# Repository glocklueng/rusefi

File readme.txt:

current binaries are always available at http://rusefi.com/build_server/

*****************************************************************************
*** Releases                                                              ***
*****************************************************************************
07/06/2015	r8554	more CAN, better console, bugfixes, performance
04/26/2015	r7938	vehicle speed sensor, stepper idle valve, lots of improvements
11/13/2014	r5327	ChibiOS/RT 2.6.6, better cold start logic, bugfixes, bugfixes, bugfixes...
06/12/2014	r3477	Precise event scheduling, protocol selection 
03/26/2014	r2413	C++, refactoring & improvements
02/23/2013	r1777	trigger is now configurable via TunerStudio
01/30/2014	r1309	true trigger angles, VBatt signal
01/12/2014	r1007	refactoring, refactoring & refactoring
12/19/2013	r605	ignition control & a little bit of CAN bus
11/08/2013	r100	Tuner Studio fuel map tuning, fuel pump control
10/14/2013	r39	USB serial bug, missing IAR files, self-containted Makefile
10/13/2013	r33	IAR project file
10/04/2013	r26	Patched ChibiOS/RT 2.6.1 sources are now included
09/23/2013	r20	Tuner Studio integration, configuraton persistence
08/30/2013	r14	initial documentation & refactoring. tunerstudio integration
08/03/2013	r13	wideband O2 input, better idling algorithm, serial-over-USB
07/05/2013	r10	Second CKP, sequential injection.
06/19/2013	r9	Initial version - batch injection & ignition with advance table lookup.

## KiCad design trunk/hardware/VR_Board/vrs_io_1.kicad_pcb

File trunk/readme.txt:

current binaries are always available at http://rusefi.com/build_server/

#Releases

| Release date  | Revision  | Details |
| ------------  | --------- | ------- |
| 02/15/2016	| r9600     | automatic warm-up fuel correction, performance improvements
| 08/31/2015	| r8725     | acceleration fuel correction, console improvements
| 07/06/2015	| r8554     | more CAN, better console, bugfixes, performance
| 04/26/2015	| r7938	    | vehicle speed sensor, stepper idle valve, lots of improvements
| 11/13/2014	| r5327	    | ChibiOS/RT 2.6.6, better cold start logic, bugfixes, bugfixes, bugfixes...
| 06/12/2014	| r3477	    | Precise event scheduling, protocol selection 
| 03/26/2014	| r2413	    | C++, refactoring & improvements
| 02/23/2013	| r1777	    | trigger is now configurable via TunerStudio
| 01/30/2014	| r1309	    | true trigger angles, VBatt signal
| 01/12/2014	| r1007	    | refactoring, refactoring & refactoring
| 12/19/2013	| r605	    | ignition control & a little bit of CAN bus
| 11/08/2013	| r100	    | Tuner Studio fuel map tuning, fuel pump control
| 10/14/2013	| r39	    | USB serial bug, missing IAR files, self-containted Makefile
| 10/13/2013	| r33	    | IAR project file
| 10/04/2013	| r26	    | Patched ChibiOS/RT 2.6.1 sources are now included
| 09/23/2013	| r20	    | Tuner Studio integration, configuraton persistence
| 08/30/2013	| r14	    | initial documentation & refactoring. tunerstudio integration
| 08/03/2013	| r13	    | wideband O2 input, better idling algorithm, serial-over-USB
| 07/05/2013	| r10	    | Second CKP, sequential injection.
| 06/19/2013	| r9	    | Initial version - batch injection & ignition with advance table lookup.

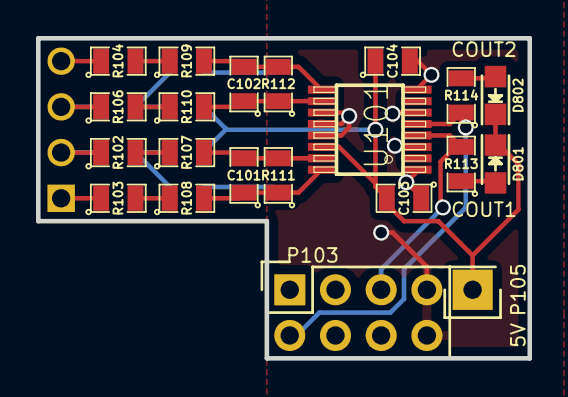
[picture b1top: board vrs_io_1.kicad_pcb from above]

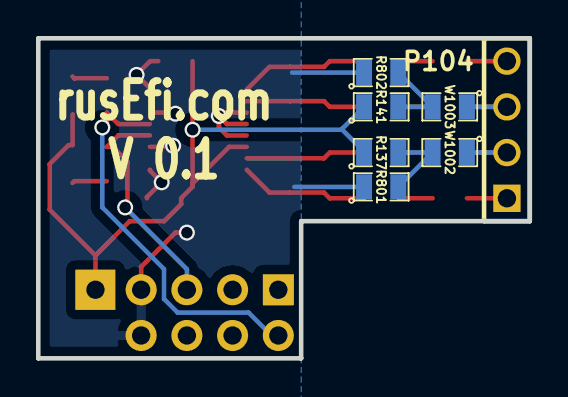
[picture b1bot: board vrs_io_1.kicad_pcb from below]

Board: 2 copper layers, 27.3 x 17.8 mm, 28 parts (7 on the bottom side), 20 nets.

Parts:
C101, C102: 1000pF; SM0805
C103: 10uF; SM0805
C104: 0.1uF; SM0805
D801, D802: LED-red; LED_0805
P103: CONN_02X04; Socket_Strip_Straight_2x04
P104: CONN_4; PIN_ARRAY_4x1
P105: CONN_01X01; Socket_Strip_Straight_1x01
R102, R103, R104, R106, R107, R108, R109, R110, R111, R112: 5k; SM0805
R113, R114: 10k; SM0805
R137, R141: 1K; SM0805
R801, R802: pdwn; SM0805
U101: MAX9926/9927; maxim-10-QSOP16
W1002, W1003: JMP; SM0805

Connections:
/5V: C103.2, C104.1, D801.1, D802.1, P105.1, R137.1, R141.1, U101.14
/CAM+: P104.4, R104.1
/CAM-: P104.3, R106.1, W1003.1
/CRK2+: P104.1, R103.1
/CRK2-: P104.2, R102.1, W1002.1
/Cout1: P103.5, R113.2, U101.4
/Cout2: P103.2, R114.1, U101.5
GND: C103.1, C104.2, P103.7, P103.8, R801.1, R802.1, U101.1, U101.3, U101.6, U101.8, U101.11, U101.12, U101.13
unnamed: C101.1, R108.2, R111.1, U101.16
unnamed: C101.2, R107.2, R111.2, U101.15
unnamed: C102.1, R110.2, R112.1, U101.10
unnamed: C102.2, R109.2, R112.2, U101.9
unnamed: D801.2, R113.1
unnamed: D802.2, R114.2
unnamed: R102.2, R107.1
unnamed: R103.2, R108.1
unnamed: R104.2, R109.1
unnamed: R106.2, R110.1
unnamed: R137.2, R801.2, W1002.2
unnamed: R141.2, R802.2, W1003.2

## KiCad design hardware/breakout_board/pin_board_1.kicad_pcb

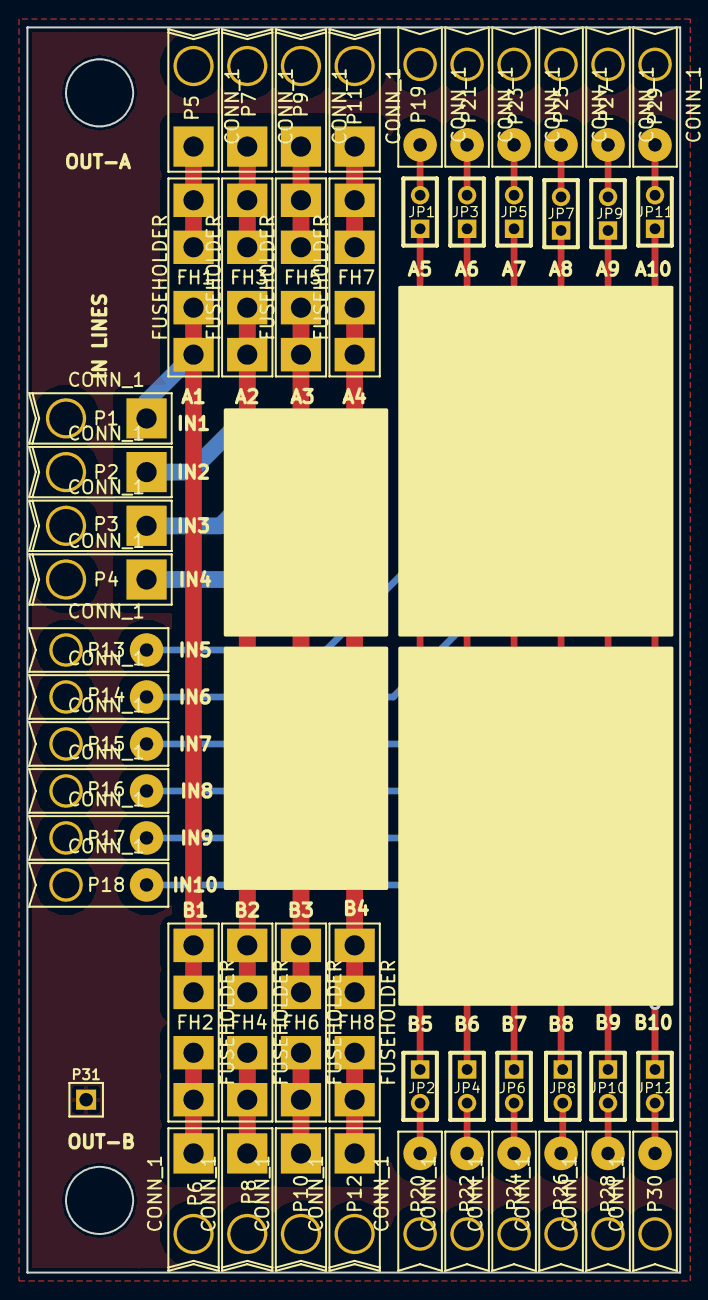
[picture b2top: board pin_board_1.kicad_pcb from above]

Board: 2 copper layers, 49.4 x 94.2 mm, 51 parts (0 on the bottom side), 30 nets.

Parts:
FH1, FH2, FH3, FH4, FH5, FH6, FH7, FH8: FUSEHOLDER
JP1, JP2, JP3, JP4, JP5, JP6, JP7, JP8, JP9, JP10, JP11, JP12: JUMPER; JUMPER-2
P1, P2, P3, P4, P5, P6, P7, P8, P9, P10, P11, P12: CONN_1; PIN_1_16AWG
P13, P14, P15, P16, P17, P18, P19, P20, P21, P22, P23, P24, P25, P26, P27, P28, P29, P30: CONN_1; PIN_1_20AWG
P31: CONN_1; PIN_ARRAY_1

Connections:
unnamed: JP8.2, P26.1
unnamed: JP7.2, P25.1
unnamed: JP7.1, JP8.1, P16.1
unnamed: JP3.2, P21.1
unnamed: JP4.2, P22.1
unnamed: JP3.1, JP4.1, P14.1
unnamed: JP5.1, JP6.1, P15.1
unnamed: JP6.2, P24.1
unnamed: JP5.2, P23.1
unnamed: JP11.2, P29.1
unnamed: JP12.2, P30.1
unnamed: JP11.1, JP12.1, P18.1
unnamed: JP10.2, P28.1
unnamed: JP9.2, P27.1
unnamed: JP9.1, JP10.1, P17.1
unnamed: JP1.2, P19.1
unnamed: JP2.2, P20.1
unnamed: FH3.1, FH4.1, P2.1
unnamed: FH4.2, P8.1
unnamed: FH3.2, P7.1
unnamed: FH1.1, FH2.1, P1.1
unnamed: FH2.2, P6.1
unnamed: FH1.2, P5.1
unnamed: JP1.1, JP2.1, P13.1
unnamed: FH7.1, FH8.1, P4.1
unnamed: FH8.2, P12.1
unnamed: FH7.2, P11.1
unnamed: FH5.1, FH6.1, P3.1
unnamed: FH6.2, P10.1
unnamed: FH5.2, P9.1

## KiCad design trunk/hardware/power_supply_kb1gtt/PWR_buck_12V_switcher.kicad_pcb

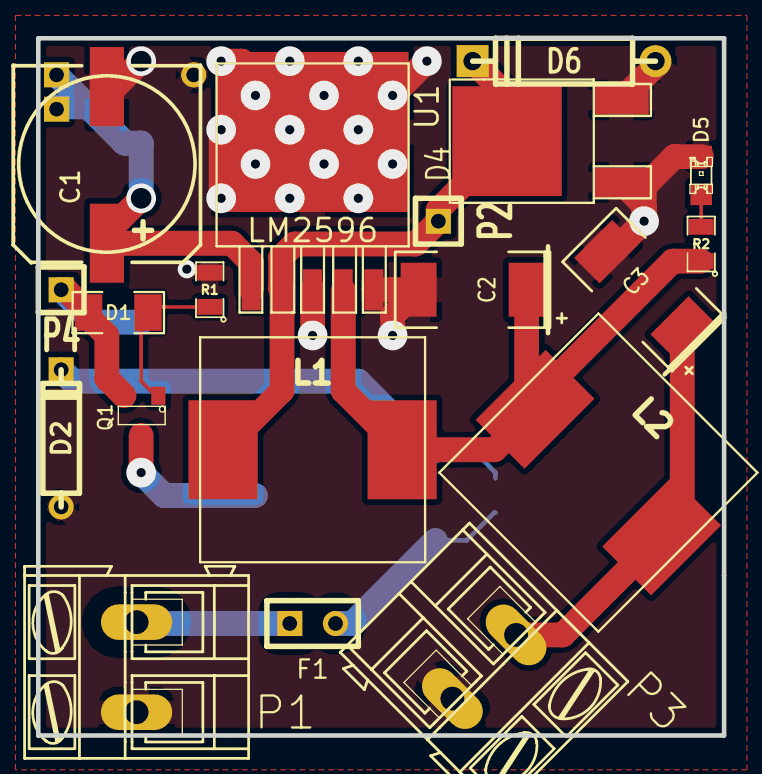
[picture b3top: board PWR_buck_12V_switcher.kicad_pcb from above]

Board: 2 copper layers, 38.1 x 38.7 mm, 24 parts (0 on the bottom side), 12 nets.

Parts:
C1: 330uF 35V; SMDSVP10
C2, C3: 220uF 16V; SM2512
D1: 7.5V; SM1206
D2: 14V; D3
D3: 24V; D3
D4: SCHDPAK; DPAK2
D5: LED-grn; LED-0805
D6: DIODESCH; D4
F1: 5A; SIL-2
L1, L2, L3: 38uH; SM100uH
P1, P3: CONN_2; AK300-2
P2, P4, P5: CONN_1; SIL-1
Q1: 20V; SOT23
Q2: 200V; m-pad-2.1-TO-263AB
R1: 39k; SM0805
R2: 1k; SM0805
R3: 100k; SM0805
U1: LM2596; DPAK5

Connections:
/5V-REG: C3.1, L2.2, P3.1
/FB: C2.1, L1.2, L2.1, R2.1, U1.4
/OUT: D4.2, D6.2, L1.1, P2.1, U1.2
/VBAT: C1.1, D3.2, L3.2, P5.1, U1.1
/Vf: F1.2, Q2.3, R3.1
/Vin: F1.1, P1.2
/Vs1: D2.2, Q2.1, R3.2
/Vs2: Q1.3, Q2.2
GND: C1.2, C2.2, C3.2, D2.1, D3.1, D4.1, D4.3, D5.2, D6.1, P1.1, P3.2, R1.2, U1.3, U1.5
unnamed: D1.1, Q1.1, R1.1
unnamed: D1.2, L3.1, P4.1, Q1.2
unnamed: D5.1, R2.2

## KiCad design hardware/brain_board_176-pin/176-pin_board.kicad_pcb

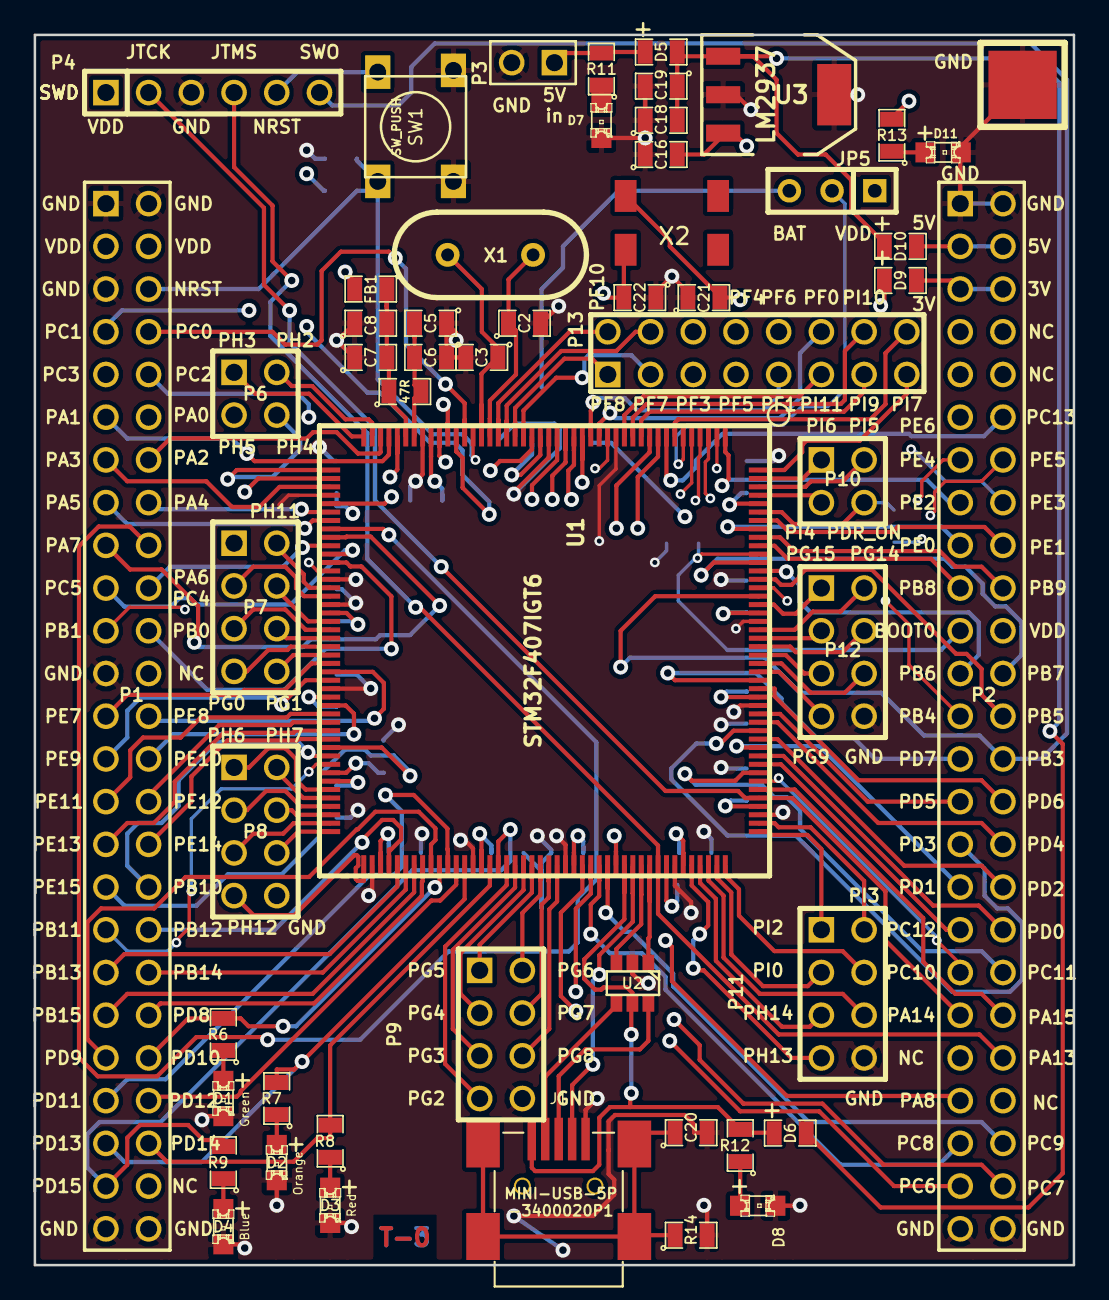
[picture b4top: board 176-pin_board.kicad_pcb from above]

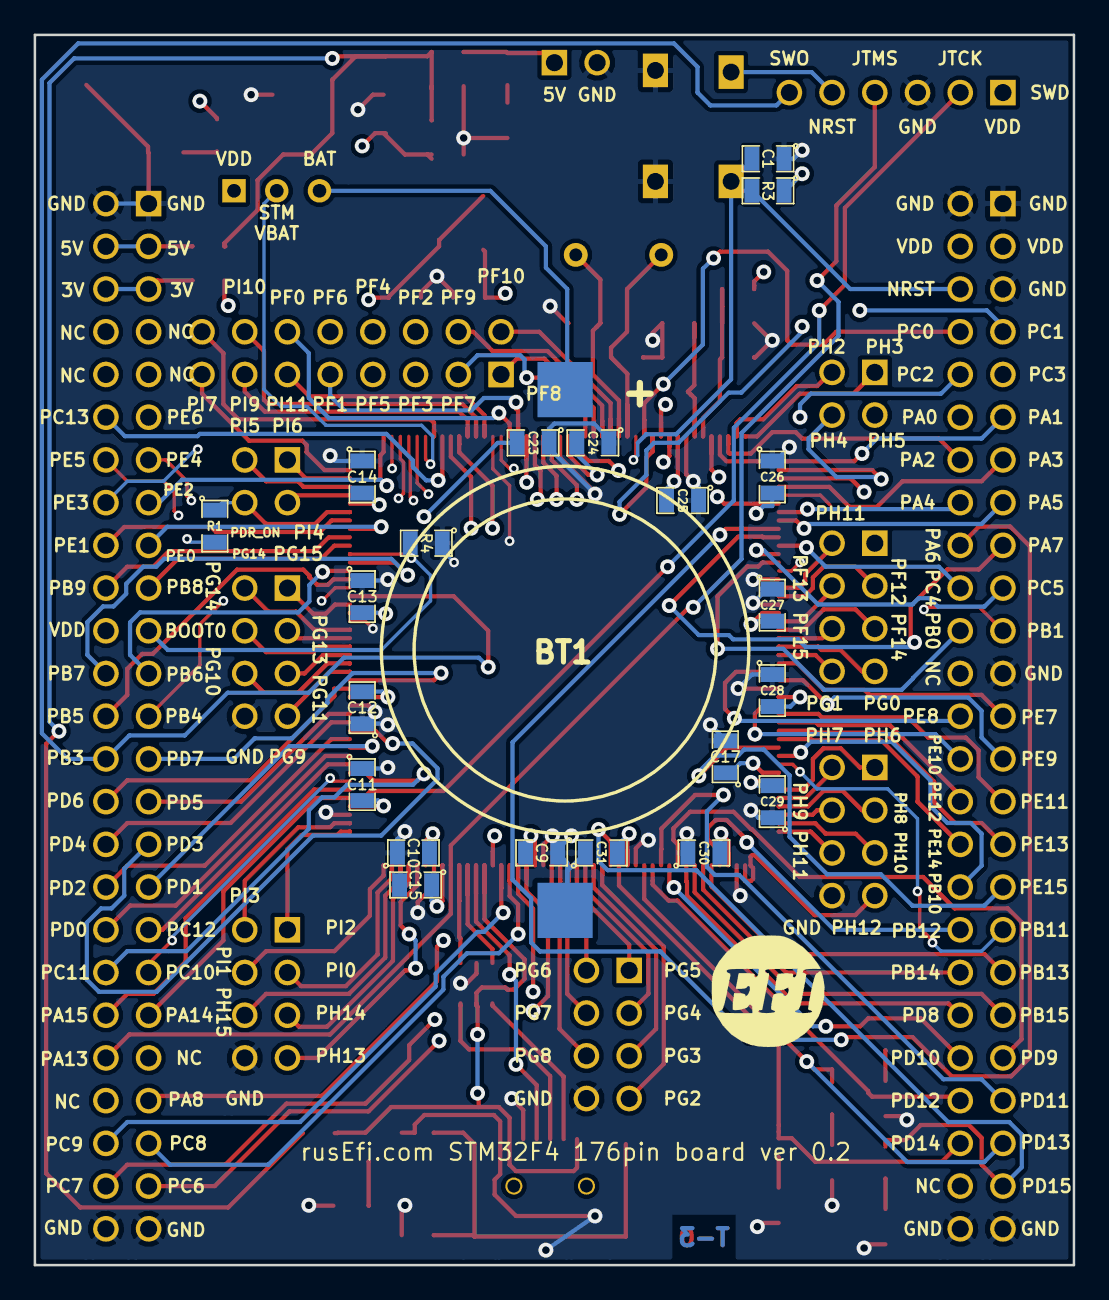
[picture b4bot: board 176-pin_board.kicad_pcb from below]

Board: 4 copper layers, 61.8 x 73.2 mm, 77 parts (23 on the bottom side), 164 nets.

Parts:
BT1: BATTERY_CR2032; BATT_CR2032_MPD
C1: 0.02uF; SM0805
C2, C3, C21, C22: 18pF; SM0805
C5, C8: 0.01uF; SM0805
C6, C7, C16: 1uF; SM0805
C9, C10, C11, C12, C13, C14, C18, C20, C23, C24, C25, C26, C27, C28, C29, C30, C31: 0.1uF; SM0805
C15, C17: 2u2F; SM0805
C19: 4.7uF; SM0805
D1, D2, D3, D4, D7, D8, D11: LED_0805; LED-0805_A
D5, D6, D9, D10: DIODESCH; SM0805-diode
FB1: FILTER; SM0805
G1: LOGO; LOGO_F
J1: MINI-USB-5P-3400020P1
JP5: JUMPER3; SIL-3
P1, P2: CONN_25X2; PIN_ARRAY_25x2_A
P3: CONN_2; PIN_ARRAY_2_A
P4: CONN_6; PIN_ARRAY-6X1
P5: CONN_1; 1PIN_SMD
P6, P10: CONN_2X2; PIN_ARRAY_2X2
P7, P8, P9, P11, P12: CONN_4X2; pin_array_4x2
P13: CONN_8X2; pin_array_8x2
R1, R11, R12, R13: 1k; SM0805
R3, R4: 10k; SM0805
R6, R7, R8, R9: 680R; SM0805
R10: 47R; SM0805
R14: 100k; SM0805
SW1: SW_PUSH; TL-1105
U1: STM32F407IGT6; LQFP-176
U2: NUF2101MT1G; SOT-457
U3: LM2937; SOT223
X1: CRYSTAL; HC-49V
X2: CRYSTAL(MC306); MC-306

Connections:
/3.3V: D9.2, P2.5, P2.6
/5V: D10.2, P2.3, P2.4
/5Vi: C18.2, C19.1, D5.2, D6.2, D10.1, U3.1
/BOOT0: P2.21, R4.2, U1.166
/D+: J1.3, U2.6
/D-: J1.2, U2.4
/NRST: C1.2, P1.6, P4.5, R3.2, SW1.1, U1.31
/PA0: P1.12, U1.40
/PA1: P1.11, U1.41
/PA2: P1.14, U1.42
/PA3: P1.13, U1.47
/PA4: P1.16, U1.50
/PA5: P1.15, U1.51
/PA6: P1.18, U1.52
/PA7: P1.17, U1.53
/PA8: P2.43, U1.119
/PA9: D6.1, J1.1, R12.2, U1.120, U2.5
/PA10: J1.4, U1.121
/PA11: U1.122, U2.3
/PA12: U1.123, U2.1
/PA13: P2.42, P4.4, U1.124
/PA14: P2.39, P4.2, U1.137
/PA15: P2.40, U1.138
/PB0: P1.22, U1.56
/PB1: P1.21, U1.57
/PB3: P2.28, P4.6, U1.161
/PB4: P2.25, U1.162
/PB5: P2.26, U1.163
/PB6: P2.23, U1.164
/PB7: P2.24, U1.165
/PB8: P2.19, U1.167
/PB9: P2.20, U1.168
/PB10: P1.34, U1.79
/PB11: P1.35, U1.80
/PB12: P1.36, U1.92
/PB13: P1.37, U1.93
/PB14: P1.38, U1.94
/PB15: P1.39, U1.95
/PC0: P1.8, U1.32
/PC1: P1.7, U1.33
/PC2: P1.10, U1.34
/PC3: P1.9, U1.35
/PC4: P1.20, U1.54
/PC5: P1.19, U1.55
/PC6: P2.47, U1.115
/PC7: P2.48, U1.116
/PC8: P2.45, U1.117
/PC9: P2.46, U1.118
/PC10: P2.37, U1.139
/PC11: P2.38, U1.140
/PC12: P2.35, U1.141
/PC13: P2.12, U1.8
/PD0: P2.36, U1.142
/PD1: P2.33, U1.143
/PD2: P2.34, U1.144
/PD3: P2.31, U1.145
/PD4: P2.32, U1.146
/PD5: P2.29, U1.147
/PD6: P2.30, U1.150
/PD7: P2.27, U1.151
/PD8: P1.40, U1.96
/PD9: P1.41, U1.97
/PD10: P1.42, R6.2, U1.98
/PD11: P1.43, U1.99
/PD12: P1.44, U1.100
/PD13: P1.45, R7.2, U1.101
/PD14: P1.46, R8.2, U1.104
/PD15: P1.47, R9.2, U1.105
/PDR_ON: P10.4, R1.1, U1.171
/PE0: P2.17, U1.169
/PE1: P2.18, U1.170
/PE2: P2.15, U1.1
/PE3: P2.16, U1.2
/PE4: P2.13, U1.3
/PE5: P2.14, U1.4
/PE6: P2.11, U1.5
/PE7: P1.25, U1.68
/PE8: P1.26, U1.69
/PE9: P1.27, U1.70
/PE10: P1.28, U1.73
/PE11: P1.29, U1.74
/PE12: P1.30, U1.75
/PE13: P1.31, U1.76
/PE14: P1.32, U1.77
/PE15: P1.33, U1.78
/PF0: P13.12, U1.16
/PF1: P13.9, U1.17
/PF2: P13.6, U1.18
/PF3: P13.5, U1.19
/PF4: P13.8, U1.20
/PF5: P13.7, U1.21
/PF6: P13.10, U1.24
/PF7: P13.3, U1.25
/PF8: P13.1, U1.26
/PF9: P13.4, U1.27
/PF10: P13.2, U1.28
/PF11: P7.2, U1.59
/PF12: P7.3, U1.60
/PF13: P7.4, U1.63
/PF14: P7.5, U1.64
/PF15: P7.6, U1.65
/PG0: P7.7, U1.66
/PG1: P7.8, U1.67
/PG2: P9.7, U1.106
/PG3: P9.5, U1.107
/PG4: P9.3, U1.108
/PG5: P9.1, U1.109
/PG6: P9.2, U1.110
/PG7: P9.4, U1.111
/PG8: P9.6, U1.112
/PG9: P12.7, U1.152
/PG10: P12.6, U1.153
/PG11: P12.5, U1.154
/PG12: P12.4, U1.155
/PG13: P12.3, U1.156
/PG14: P12.2, U1.157
/PG15: P12.1, U1.160
/PH0: C2.1, U1.29, X1.2
/PH1: C3.1, U1.30, X1.1
/PH2: P6.2, U1.43
/PH3: P6.1, U1.44
/PH4: P6.4, U1.45
/PH5: P6.3, U1.46
/PH6: P8.1, U1.83
/PH7: P8.2, U1.84
/PH8: P8.3, U1.85
/PH9: P8.4, U1.86
/PH10: P8.5, U1.87
/PH11: P8.6, U1.88
/PH12: P8.7, U1.89
/PH13: P11.7, U1.128
/PH14: P11.5, U1.129
/PH15: P11.6, U1.130
/PI0: P11.3, U1.131
/PI1: P11.4, U1.132
/PI2: P11.1, U1.133
/PI3: P11.2, U1.134
/PI4: P10.3, U1.173
/PI5: P10.2, U1.174
/PI6: P10.1, U1.175
/PI7: P13.15, U1.176
/PI8: P13.16, U1.7
/PI9: P13.13, U1.11
/PI10: P13.14, U1.12
/PI11: P13.11, U1.13
/VBAT: JP5.2, U1.6
/VDD: C9.2, C10.2, C11.2, C12.2, C13.2, C14.2, C16.2, C23.2, C24.2, C25.2, C26.2, C27.2, C28.2, C29.2, C30.2, C31.2, D9.1, FB1.2, JP5.1, P1.3, P1.4, P2.22, P4.1, R1.2, R3.1, R13.2, U1.15, U1.23, U1.36, U1.49, U1.62, U1.72, U1.82, U1.91, U1.103, U1.114, U1.127, U1.136, U1.149, U1.159, U1.172, U3.3
GND: BT1.2, C1.1, C2.2, C3.2, C5.1, C6.1, C7.1, C8.1, C9.1, C10.1, C11.1, C12.1, C13.1, C14.1, C15.2, C16.1, C17.2, C18.1, C19.2, C20.2, C21.1, C22.1, C23.1, C24.1, C25.1, C26.1, C27.1, C28.1, C29.1, C30.1, C31.1, D1.2, D2.2, D3.2, D4.2, D7.2, D8.2, D11.2, J1.5, P1.1, P1.2, P1.5, P1.23, P1.49, P1.50, P2.1, P2.2, P2.49, P2.50, P3.2, P4.3, P5.1, P8.8, P9.8, P11.8, P12.8, R4.1, R14.2, SW1.2, U1.14, U1.22, U1.37, U1.48, U1.58, U1.61, U1.71, U1.90, U1.102, U1.113, U1.126, U1.135, U1.148, U1.158, U2.2, U3.2, U3.4
unnamed: C7.2, C8.2, FB1.1, R10.1, U1.39
unnamed: D11.1, R13.1
unnamed: D2.1, R7.1
unnamed: D1.1, R6.1
unnamed: C5.2, C6.2, R10.2, U1.38
unnamed: D3.1, R8.1
unnamed: D5.1, P3.1, R11.2
unnamed: BT1.1, JP5.3
unnamed: D4.1, R9.1
unnamed: D7.1, R11.1
unnamed: D8.1, R12.1
unnamed: C20.1, J1.6, R14.1
unnamed: C21.2, U1.9, X2.4
unnamed: C22.2, U1.10, X2.1
unnamed: C15.1, U1.125
unnamed: C17.1, U1.81

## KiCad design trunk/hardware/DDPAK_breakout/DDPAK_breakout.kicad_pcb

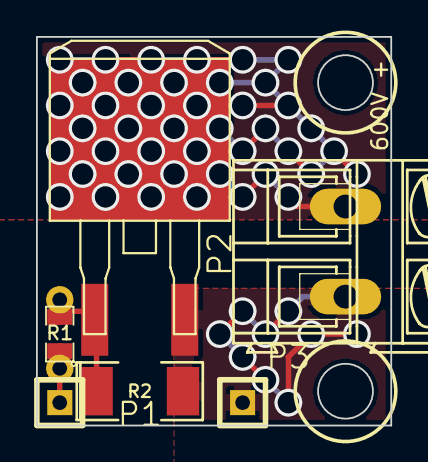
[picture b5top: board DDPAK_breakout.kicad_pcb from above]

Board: 2 copper layers, 19.7 x 21.6 mm, 6 parts (0 on the bottom side), 4 nets.

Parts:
P1, P3: CONN_1; SIL-1
P2: CONN_2; AK300-2
Q1: IRGS14C40L; m-pad-2.1-TO-263AB
R1: 1K; SM0805_jumper
R2: 100K; SM2010

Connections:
/GND: P2.2, P3.1, Q1.3, R2.2
/HV: P2.1, Q1.2
/SIG: P1.1, R1.1
/SIG2: Q1.1, R1.2, R2.1

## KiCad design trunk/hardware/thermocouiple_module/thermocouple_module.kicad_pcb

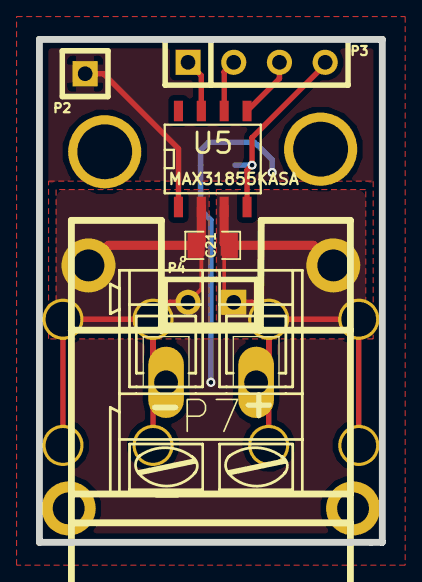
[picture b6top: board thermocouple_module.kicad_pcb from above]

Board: 2 copper layers, 19.0 x 27.9 mm, 12 parts (1 on the bottom side), 7 nets.

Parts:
C8: 100nF; SM0805-SM0603
C21: 10nF; SM0805-SM0603
P1: CONN_2; tcpl_PCC-SMP
P2: CONN_1; SIL-1
P3: CONN_4; SIL-4
P4: CONN_2; SIL-2
P5, P6: CONN_1; SCREW_TERM_534-7693
P7: CONN_2; AK300-2
U5: MAX31855KASA; SO8E
V801, V802: VIA; 1pin

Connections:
3.3v: C8.1, P3.4, U5.4
//CS: P3.2, U5.6
/MISO: P3.1, U5.7
/SCK: P3.3, U5.5
/TCPL+: C21.2, P1.2, P4.1, P6.1, P7.1, U5.3
/TCPL-: C21.1, P1.1, P4.2, P5.1, P7.2, U5.2
GND: C8.2, P2.1, U5.1

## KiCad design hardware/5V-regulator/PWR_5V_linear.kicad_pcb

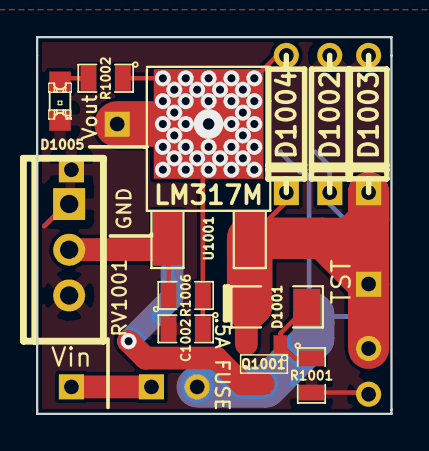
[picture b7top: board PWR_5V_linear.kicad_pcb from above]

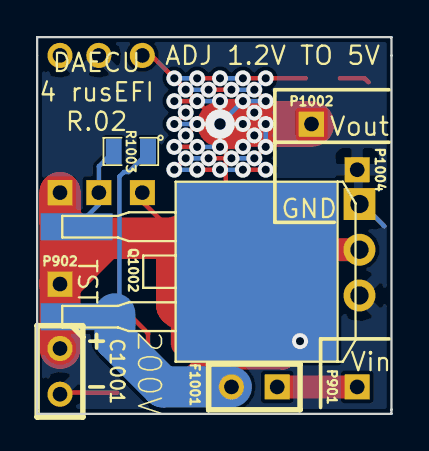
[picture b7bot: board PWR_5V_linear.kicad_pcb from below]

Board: 2 copper layers, 19.7 x 20.9 mm, 20 parts (8 on the bottom side), 10 nets.

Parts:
C1001: 0.1uF 50V; C1
C1002: 1uF 16V; SM0805
D1001: 7.5V; SM1206
D1002: 15V; D3
D1003, D1004: 24V; D3
D1005: LED-grn; LED-0805
F1001: 5A; SIL-2
P901, P902, P1002, P1004: CONN_1; SIL-1
Q1001: 30V; SOT23
Q1002: 200V; m-pad-2.1-TO-263AB
R1001, R1002: 1k; SM0805
R1003: 100k; SM0805
R1006: 240R; SM0805
RV1001: 1k; TO220_VERT
U1001: LM317M; DPAK2

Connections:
/5V-REG: C1002.1, D1004.1, P1002.1, R1002.1, R1006.2, U1001.2
/VBAT: C1001.1, D1001.2, D1003.2, D1004.2, P902.1, Q1001.2, U1001.3
/Vf: F1001.2, Q1002.3, R1003.1
/Vin: F1001.1, P901.1
/Vs1: D1002.2, Q1002.1, R1003.2
/Vs2: Q1001.3, Q1002.2
GND: C1001.2, C1002.2, D1002.1, D1003.1, D1005.2, P1004.1, R1001.2, RV1001.1, RV1001.2
unnamed: R1006.1, RV1001.3, U1001.1
unnamed: D1001.1, Q1001.1, R1001.1
unnamed: D1005.1, R1002.2

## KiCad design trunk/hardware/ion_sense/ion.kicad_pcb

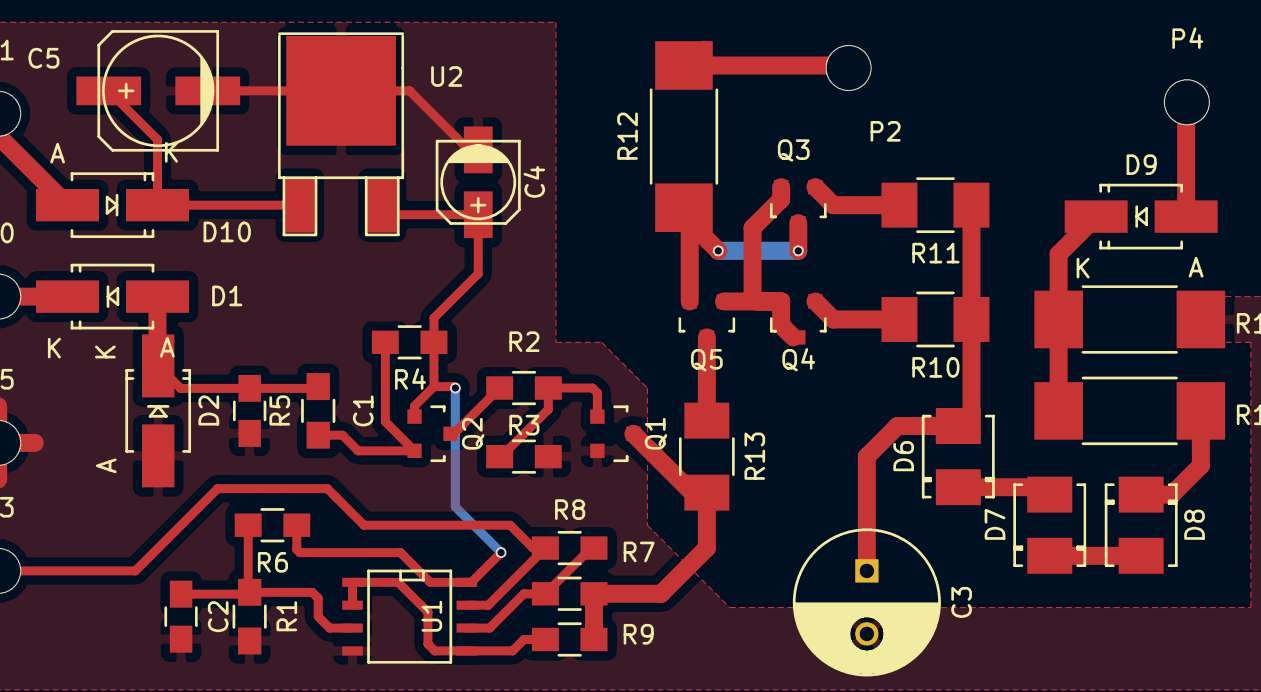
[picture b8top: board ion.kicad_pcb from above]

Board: 2 copper layers, 40 parts (0 on the bottom side), 25 nets.

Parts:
C1: 0.1uF; C_0805_HandSoldering
C2: 1uF; C_0805_HandSoldering
C3: 2.2uF 350V; C_Radial_D8_L11.5_P3.5
C4: 4.7uF 16V; c_elec_4x4.5
C5: 47uF 25V; c_elec_6.3x4.5
D1, D2, D9, D10: US1M; SMA_Handsoldering
D6, D7, D8: 1N4740A; DO-214BA
P0, P1, P2, P3, P4, P5: CONN_01X01; MountingHole_2-5mm
Q1: MMBT3904; SOT-23
Q2, Q3, Q4, Q5: MPSA92; SOT-23
R1, R6, R7, R8: 51k; R_0805_HandSoldering
R2: 2k; R_0805_HandSoldering
R3: 3.9k; R_0805_HandSoldering
R4: 10k; R_0805_HandSoldering
R5: 1k; R_0805_HandSoldering
R9: 4.7k; R_0805_HandSoldering
R10, R11: 560; R_1210_HandSoldering
R12: 180k; R_2512_HandSoldering
R13: 68k; R_1210_HandSoldering
R14: 33k; R_2512_HandSoldering
R15: 1M; R_2512_HandSoldering
U1: LM2904; SOIC-8-N
U2: MC78M05CDT; TO-252-2Lead

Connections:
Earth: C1.2, C2.2, C3.2, C4.2, C5.2, D2.2, P5.1, Q1.2, R1.2, R2.2, R15.1, U1.4, U2.2
unnamed: C1.1, D1.2, D2.1, R5.2
unnamed: C2.1, R1.1, R6.2, U1.3
unnamed: C3.1, D6.2, R10.1, R11.1
unnamed: C4.1, Q2.1, R4.1, R6.1, U1.8, U2.3
unnamed: C5.1, D10.1, U2.1
unnamed: D1.1, P0.1
unnamed: D6.1, D7.2
unnamed: D7.1, D8.2
unnamed: D8.1, R14.2
unnamed: D9.1, R14.1, R15.2
unnamed: D9.2, P4.1
unnamed: D10.2, P1.1
unnamed: P3.1, R8.1, U1.7
unnamed: Q1.1, R2.1, R3.1
unnamed: Q1.3, R7.1, R9.1, R13.2
unnamed: Q2.2, R4.2, R5.1
unnamed: Q2.3, R3.2
unnamed: Q3.1, R11.2
unnamed: Q3.2, Q4.2, Q4.3, Q5.1
unnamed: Q3.3, Q5.2, R12.1
unnamed: Q4.1, R10.2
unnamed: Q5.3, R13.1
unnamed: R7.2, R8.2, U1.6
unnamed: R9.2, U1.1, U1.2, U1.5

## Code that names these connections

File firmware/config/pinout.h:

/*
 * pinout.h
 *
 *  Created on: Aug 29, 2013
 *      Author: Andrey Belomutskiy, (c) 2012-2013
 */

#ifndef PINOUT_H_
#define PINOUT_H_

#if EFI_SHAFT_POSITION_INPUT
/**
 * currently ChibiOS uses only first channel of each timer for input capture
 *
 * So, our options are:
 *
 * TIM2_CH1
 *  PA5
 *
 * TIM4_CH1
 *  PB6
 * 	PD12
 *
 * TIM9_CH1
 *  PE5
 */

#endif

#define IDLE_SWITCH_PORT GPIOC
#define IDLE_SWITCH_PIN 8

#endif /* PINOUT_H_ */

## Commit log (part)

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2016-03-09 docs
2016-03-10 festiva
2016-03-10 fixing TDC position
2016-03-10 refactoring
2016-03-10 fixing build
2016-03-10 accel unit test
2016-03-10 accel progress
2016-03-10 acceleration enrichment progress
2016-03-10 improving test
2016-03-11 bugfix
2016-03-11 progress
2016-03-11 fixing simulator
2016-03-11 refactoring: better parameter order
2016-03-12 map acceleration taper
2016-03-13 load change gauge
2016-03-13 individual
2016-03-15 #268 TS io testing
2016-03-16 #275 cranking could be improved
2016-03-17 #272 boost cut
2016-03-18 IAR is happy
2016-03-20 new dialog "tuning"->"console monitoring"
2016-03-21 starter relay
2016-03-21 bugfix & better error handling
2016-03-22 #127 FSIO: add user-defined maps
2016-03-22 tiny progress
2016-03-22 fixes
2016-03-22 bugfix with debugMode
2016-03-26 Geo Storm
2016-04-01 ChibiOS 3.0
2016-04-01 chibi 3.0
2016-04-03 happy new year
2016-04-03 reducing IO mess
2016-04-03 todo
2016-04-03 making progress
2016-04-03 now reading configuration is the first thing we do
2016-04-03 code style
2016-04-03 bugfix?
2016-04-03 fixing kalina
2016-04-07 #112
2016-04-09 comments
2016-04-09 trigger counter to TS
2016-04-09 misc
2016-04-09 better error logging
2016-04-10 moving to 4.0
2016-04-12 #262 configuration setting to disable text protocol
2016-04-12 #281 better FATAL error handling
2016-04-14 http://kicad-users.yahoogroups.narkive.com/OHuIAYkP/components-missing-in-position-file
2016-04-16 BUGFIX - debug version would not start on erased chip
2016-04-16 poke
2016-04-16 #121 dev console to write TS compatible logs
2016-04-16 miata 1.6
2016-04-18 reboot warning
2016-04-18 merge
2016-04-18 better formating
2016-04-19 warning light
2016-04-19 FSIO eval bugfix
2016-04-20 shift light
2016-04-21 more info into the log
2016-04-22 warning light festiva
2016-04-23 vbatt into defaults
2016-04-23 correcting pin comments
2016-04-23 better analoginfo text
2016-04-23 LCD menu tiny progress
2016-04-23 injectorDutyCycle into log file
2016-04-23 better error message
